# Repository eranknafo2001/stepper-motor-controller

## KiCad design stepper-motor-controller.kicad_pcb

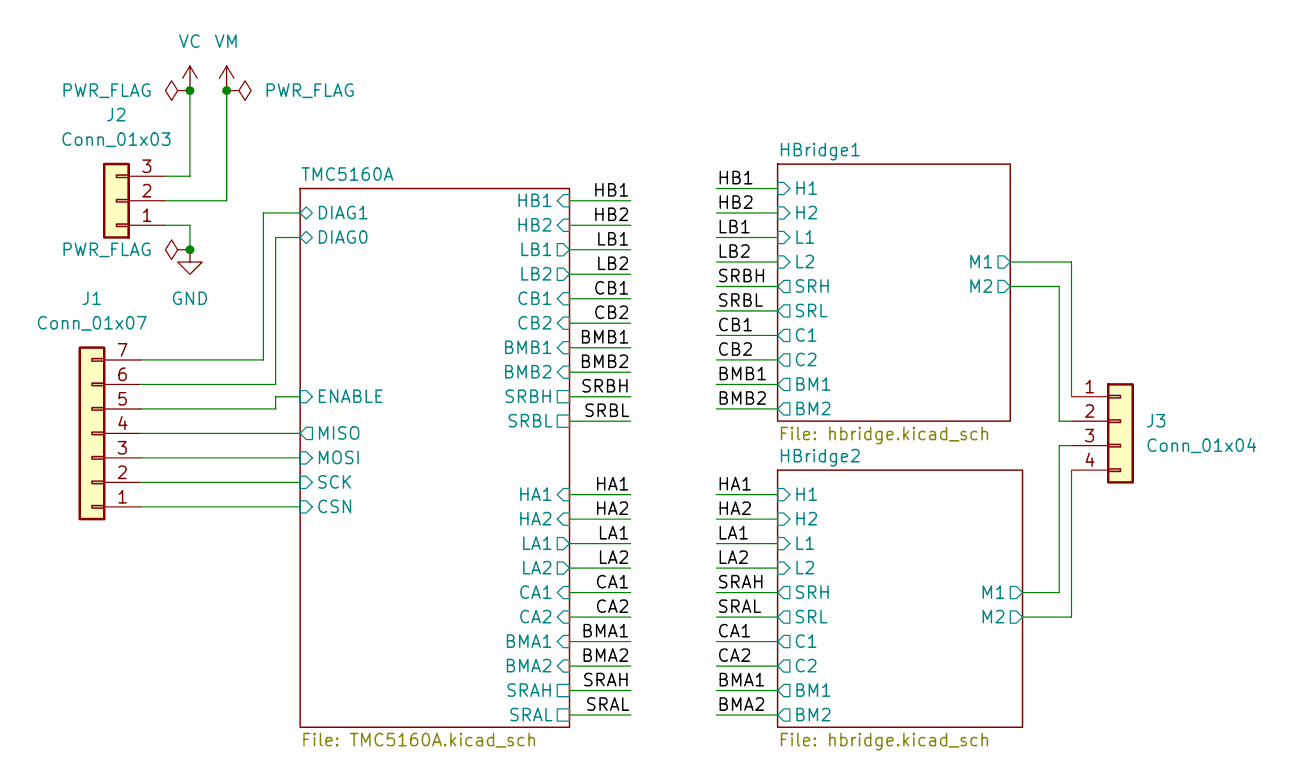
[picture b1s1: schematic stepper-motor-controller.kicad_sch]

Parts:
J1: Conn_01x07; PinHeader_1x07_P2.54mm_Vertical
J2: Conn_01x03; PinHeader_1x03_P2.54mm_Vertical
J3: Conn_01x04; PinHeader_1x04_P2.54mm_Vertical; LCSC Part C7500810

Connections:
/BMA1: J3.3; also elsewhere on the board
/BMA2: J3.4; also elsewhere on the board
/BMB1: J3.1; also elsewhere on the board
/BMB2: J3.2; also elsewhere on the board
/TMC5160A/CSN: J1.1; also elsewhere on the board
/TMC5160A/DIAG0: J1.6; also elsewhere on the board
/TMC5160A/DIAG1: J1.7; also elsewhere on the board
/TMC5160A/ENABLE: J1.5; also elsewhere on the board
/TMC5160A/MISO: J1.4; also elsewhere on the board
/TMC5160A/MOSI: J1.3; also elsewhere on the board
/TMC5160A/SCK: J1.2; also elsewhere on the board
GND: J2.1; also elsewhere on the board
VC: J2.3; also elsewhere on the board
VM: J2.2; also elsewhere on the board

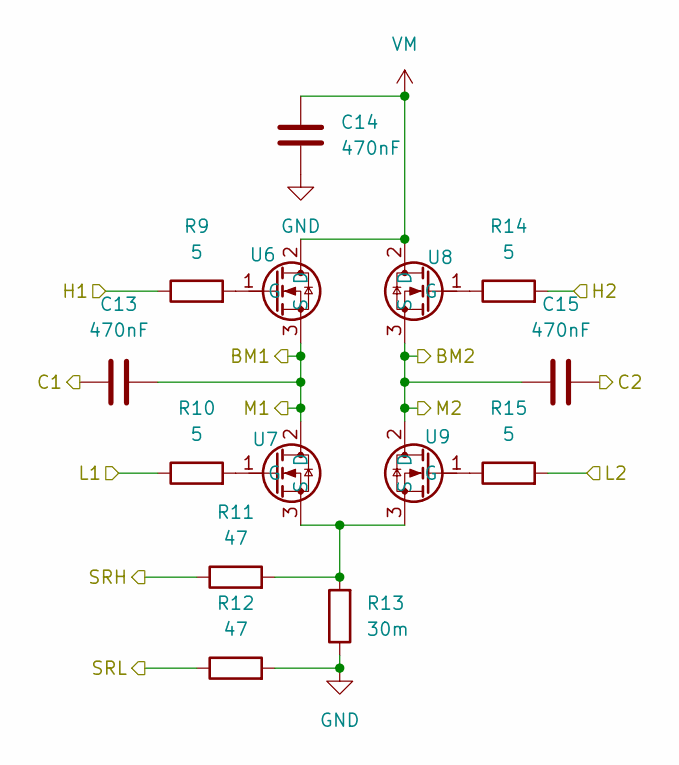
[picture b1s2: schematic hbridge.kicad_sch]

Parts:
C13, C14, C15: 470nF; C_0603_1608Metric_Pad1.08x0.95mm_HandSolder; LCSC Part C7503496
R9, R10, R14, R15: 5; R_2512_6332Metric_Pad1.40x3.35mm_HandSolder; LCSC Part C5123609
R11, R12: 47; R_0603_1608Metric_Pad0.98x0.95mm_HandSolder; LCSC Part C2907174
R13: 30m; R_0603_1608Metric_Pad0.98x0.95mm_HandSolder; LCSC Part C5126263
U6, U7, U8, U9: AOD4126; TRANS_TSM60N1R4CP_ROG; LCSC Part C41407552

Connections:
/BMA1: C13.2, U6.3 (S), U7.2 (D); also elsewhere on the board
/BMA2: C15.1, U8.3 (S), U9.2 (D); also elsewhere on the board
/CA1: C13.1; also elsewhere on the board
/CA2: C15.2; also elsewhere on the board
/HA1: R9.1; also elsewhere on the board
/HA2: R14.2; also elsewhere on the board
/LA1: R10.1; also elsewhere on the board
/LA2: R15.2; also elsewhere on the board
/SRAH: R11.1; also elsewhere on the board
/SRAL: R12.1; also elsewhere on the board
GND: C14.1, R12.2, R13.1; also elsewhere on the board
unnamed: R9.2, U6.1 (G)
unnamed: R10.2, U7.1 (G)
unnamed: R11.2, R13.2, U7.3 (S), U9.3 (S)
unnamed: R14.1, U8.1 (G)
unnamed: R15.1, U9.1 (G)
VM: C14.2, U6.2 (D), U8.2 (D); also elsewhere on the board

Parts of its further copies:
C3, C8, C12: 470nF; C_0603_1608Metric_Pad1.08x0.95mm_HandSolder; LCSC Part C7503496
R1, R2, R7, R8: 5; R_2512_6332Metric_Pad1.40x3.35mm_HandSolder; LCSC Part C5123609
R4, R5: 47; R_0603_1608Metric_Pad0.98x0.95mm_HandSolder; LCSC Part C2907174
R6: 30m; R_0603_1608Metric_Pad0.98x0.95mm_HandSolder; LCSC Part C5126263
U1, U2, U3, U4: AOD4126; TRANS_TSM60N1R4CP_ROG; LCSC Part C41407552

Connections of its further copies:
/BMB1: C3.2, U1.3 (S), U2.2 (D); also elsewhere on the board
/BMB2: C12.1, U3.3 (S), U4.2 (D); also elsewhere on the board
/CB1: C3.1; also elsewhere on the board
/CB2: C12.2; also elsewhere on the board
/HB1: R1.1; also elsewhere on the board
/HB2: R7.2; also elsewhere on the board
/LB1: R2.1; also elsewhere on the board
/LB2: R8.2; also elsewhere on the board
/SRBH: R4.1; also elsewhere on the board
/SRBL: R5.1; also elsewhere on the board
GND: C8.1, R5.2, R6.1; also elsewhere on the board
unnamed: R1.2, U1.1 (G)
unnamed: R2.2, U2.1 (G)
unnamed: R4.2, R6.2, U2.3 (S), U4.3 (S)
unnamed: R7.1, U3.1 (G)
unnamed: R8.1, U4.1 (G)
VM: C8.2, U1.2 (D), U3.2 (D); also elsewhere on the board

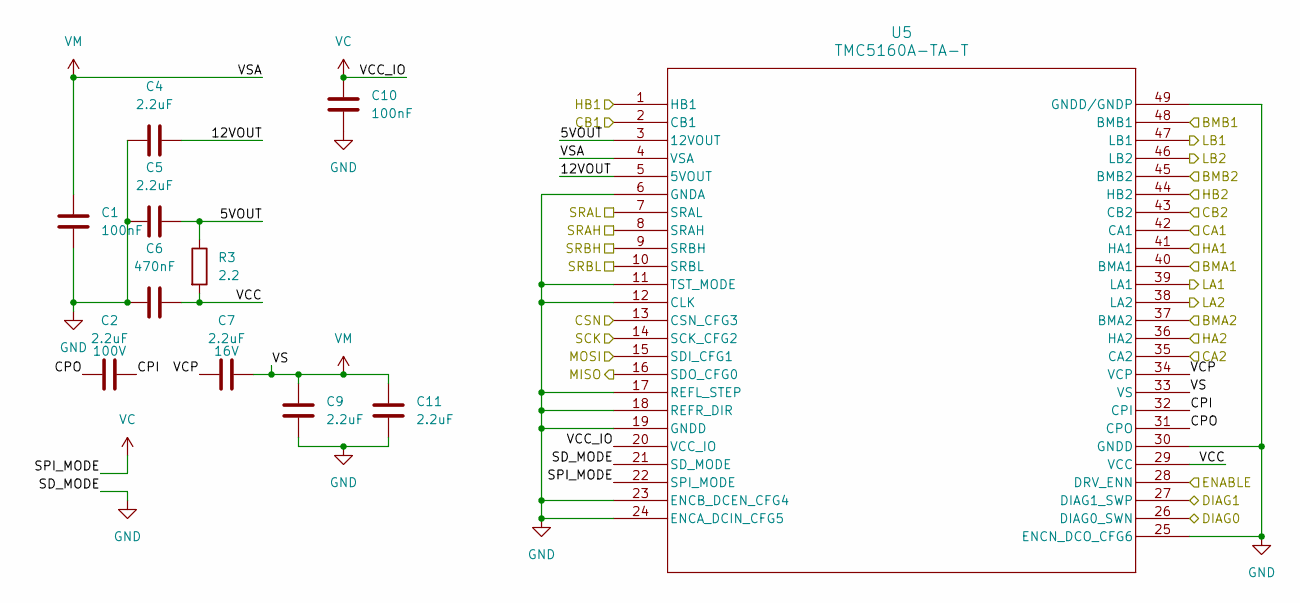
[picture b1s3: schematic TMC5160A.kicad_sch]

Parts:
C1, C10: 100nF; C_0603_1608Metric_Pad1.08x0.95mm_HandSolder; LCSC Part C6119867
C2: 2.2uF; C_0805_2012Metric_Pad1.18x1.45mm_HandSolder; Voltage 100V; LCSC Part C2981733
C4, C5, C9, C11: 2.2uF; C_0603_1608Metric_Pad1.08x0.95mm_HandSolder; LCSC Part C57895
C6: 470nF; C_0603_1608Metric_Pad1.08x0.95mm_HandSolder
C7: 2.2uF; C_0603_1608Metric_Pad1.08x0.95mm_HandSolder; Voltage 16V; LCSC Part C23630
R3: 2.2; R_0603_1608Metric_Pad0.98x0.95mm_HandSolder; LCSC Part C2930032
U5: TMC5160A-TA-T; 21-100582_ADI; LCSC Part C516354

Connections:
/BMA1: U5.40 (BMA1); also elsewhere on the board
/BMA2: U5.37 (BMA2); also elsewhere on the board
/BMB1: U5.48 (BMB1); also elsewhere on the board
/BMB2: U5.45 (BMB2); also elsewhere on the board
/CA1: U5.42 (CA1); also elsewhere on the board
/CA2: U5.35 (CA2); also elsewhere on the board
/CB1: U5.2 (CB1); also elsewhere on the board
/CB2: U5.43 (CB2); also elsewhere on the board
/HA1: U5.41 (HA1); also elsewhere on the board
/HA2: U5.36 (HA2); also elsewhere on the board
/HB1: U5.1 (HB1); also elsewhere on the board
/HB2: U5.44 (HB2); also elsewhere on the board
/LA1: U5.39 (LA1); also elsewhere on the board
/LA2: U5.38 (LA2); also elsewhere on the board
/LB1: U5.47 (LB1); also elsewhere on the board
/LB2: U5.46 (LB2); also elsewhere on the board
/SRAH: U5.8 (SRAH); also elsewhere on the board
/SRAL: U5.7 (SRAL); also elsewhere on the board
/SRBH: U5.9 (SRBH); also elsewhere on the board
/SRBL: U5.10 (SRBL); also elsewhere on the board
/TMC5160A/5VOUT: C5.2, R3.1, U5.3 (12VOUT)
/TMC5160A/12VOUT: C4.2, U5.5 (5VOUT)
/TMC5160A/CPI: C2.2, U5.32 (CPI)
/TMC5160A/CPO: C2.1, U5.31 (CPO)
/TMC5160A/CSN: U5.13 (CSN_CFG3); also elsewhere on the board
/TMC5160A/DIAG0: U5.26 (DIAG0_SWN); also elsewhere on the board
/TMC5160A/DIAG1: U5.27 (DIAG1_SWP); also elsewhere on the board
/TMC5160A/ENABLE: U5.28 (DRV_ENN); also elsewhere on the board
/TMC5160A/MISO: U5.16 (SDO_CFG0); also elsewhere on the board
/TMC5160A/MOSI: U5.15 (SDI_CFG1); also elsewhere on the board
/TMC5160A/SCK: U5.14 (SCK_CFG2); also elsewhere on the board
/TMC5160A/VCC: C6.2, R3.2, U5.29 (VCC)
/TMC5160A/VCP: C7.1, U5.34 (VCP)
GND: C1.1, C4.1, C5.1, C6.1, C9.1, C10.1, C11.1, U5.6 (GNDA), U5.11 (TST_MODE), U5.12 (CLK), U5.17 (REFL_STEP), U5.18 (REFR_DIR), U5.19 (GNDD), U5.21 (SD_MODE), U5.23 (ENCB_DCEN_CFG4), U5.24 (ENCA_DCIN_CFG5), U5.25 (ENCN_DCO_CFG6), U5.30 (GNDD), U5.49 (GNDD/GNDP); also elsewhere on the board
VC: C10.2, U5.20 (VCC_IO), U5.22 (SPI_MODE); also elsewhere on the board
VM: C1.2, C7.2, C9.2, C11.2, U5.4 (VSA), U5.33 (VS); also elsewhere on the board

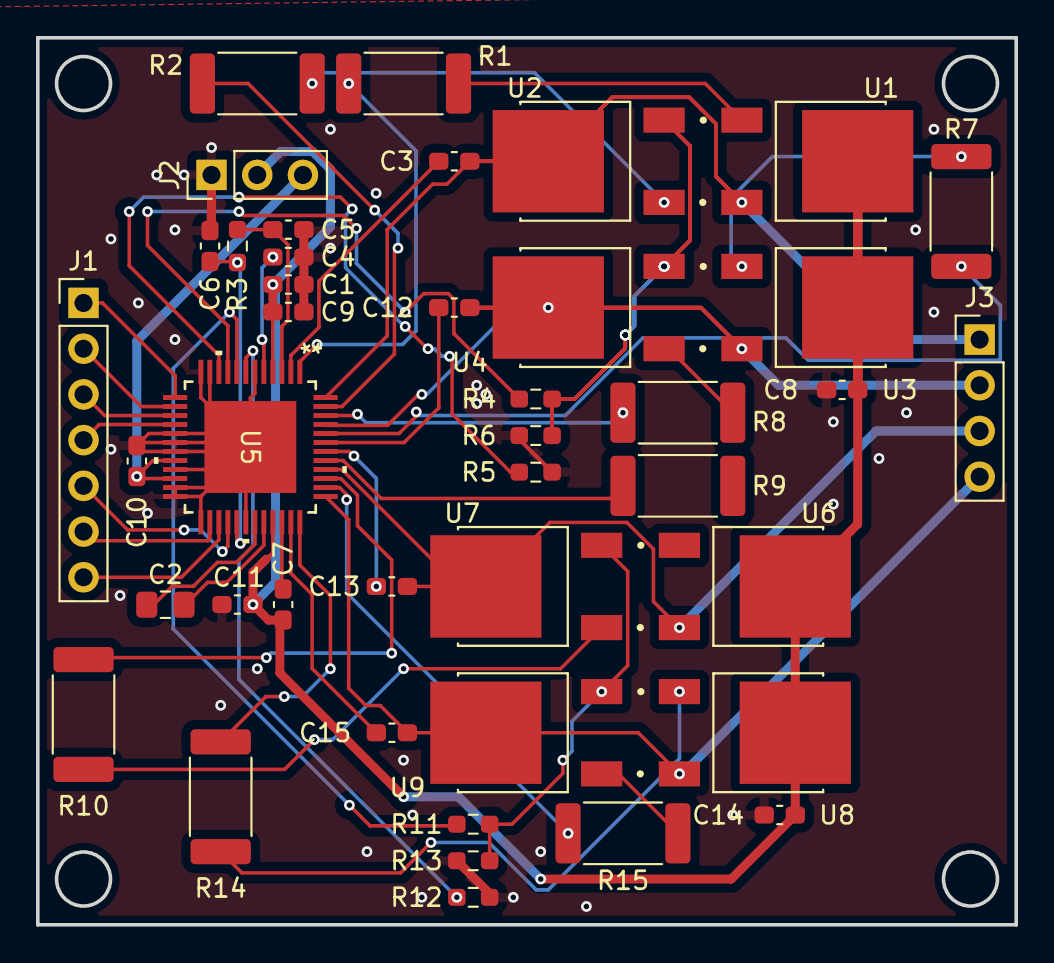
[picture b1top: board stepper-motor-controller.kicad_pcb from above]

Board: 2 copper layers, 54.4 x 49.3 mm, 42 parts (0 on the bottom side), 46 nets.
